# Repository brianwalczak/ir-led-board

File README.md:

# `ir-led-board`
A custom circuit connecting 16 high-current IR LEDs, designed for integration with Raspberry Pi and imaging projects.

Check out my [JOURNAL.md](JOURNAL.md) for updates and progress!

> [!NOTE]  
> All custom footprints in this project, as well as 3D print files, were created by me and are freely available under the MIT license. You are completely welcome to use, modify, and distribute them without any restrictions.

#### PCB Design
A custom-designed printed circuit board, designed in KiCad 9.0, allowing you to control 16 IR LEDs in groups of four. This PCB was designed as an easy way to connect the components and use them via GPIO pins on the Raspberry Pi.

👉 [Read More](KiCad_PCB/README.md)

#### 3D Model (case)
A 3D printable case, designed in Fusion 360, made to securely hold the board and its components, as well as providing protection to prevent damage to the board.

<br>

👉 [Read More](3D_Print/README.md)

#### Bill of Materials (BOM)

| Qty | Part Number                | Total Price |
|-----|------------------------------------------|-------------|
| 5   | JLCPCB: PCB Print               | $5.30      |
| 1   | Raspberry Pi Camera 3 NoIR               | $25.00      |
| 1   | Raspberry Pi 5 Camera Cable              | $1.10       |
| 16  | SFH 4556-AW (850nm IR LEDs)              | $9.47       |
| 16  | CFM12JT43R0 (43 Ohms resistor)           | $0.58       |
| 4   | IRLB8743PBF (MOSFETs)                    | $4.76       |
| 4   | DC0011 (thermal pads)                    | $2.20       |
| 4   | CF14JT100R (100 Ohms resistor)           | $0.24       |
| 4   | CF14JT100K (100K Ohms resistor)          | $0.24       |
| 1   | PPPC061LGBN-RC (90-degree connector)     | $0.57       |
|     | **Total**                                | **$49.46**  |

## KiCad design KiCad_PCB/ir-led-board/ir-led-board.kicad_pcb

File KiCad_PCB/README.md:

# `ir-led-board` - KiCad PCB
> [!NOTE]  
> All custom footprints in this project were created by me and are freely available under the MIT license. You are completely welcome to use, modify, and distribute them without any restrictions.

Welcome! This folder includes a custom-designed printed circuit board for the `ir-led-board`, allowing you to control 16 IR LEDs in groups of four. This PCB was designed as an easy way to connect the components and use them via GPIO pins on the Raspberry Pi.

This PCB was designed in KiCad (you can import it with `File > Open Project` and exported as a ready-to-print Gerber file. This PCB can be printed for about **~$2.00** (quantity of 5) on [JLCPCB](https://jlcpcb.com/) (not sponsored).

**All routing has been automatically done by [Freerouting](https://github.com/freerouting/freerouting): an open-source auto-router for KiCad, built with Java.**

#### Schematic

#### PCB Design

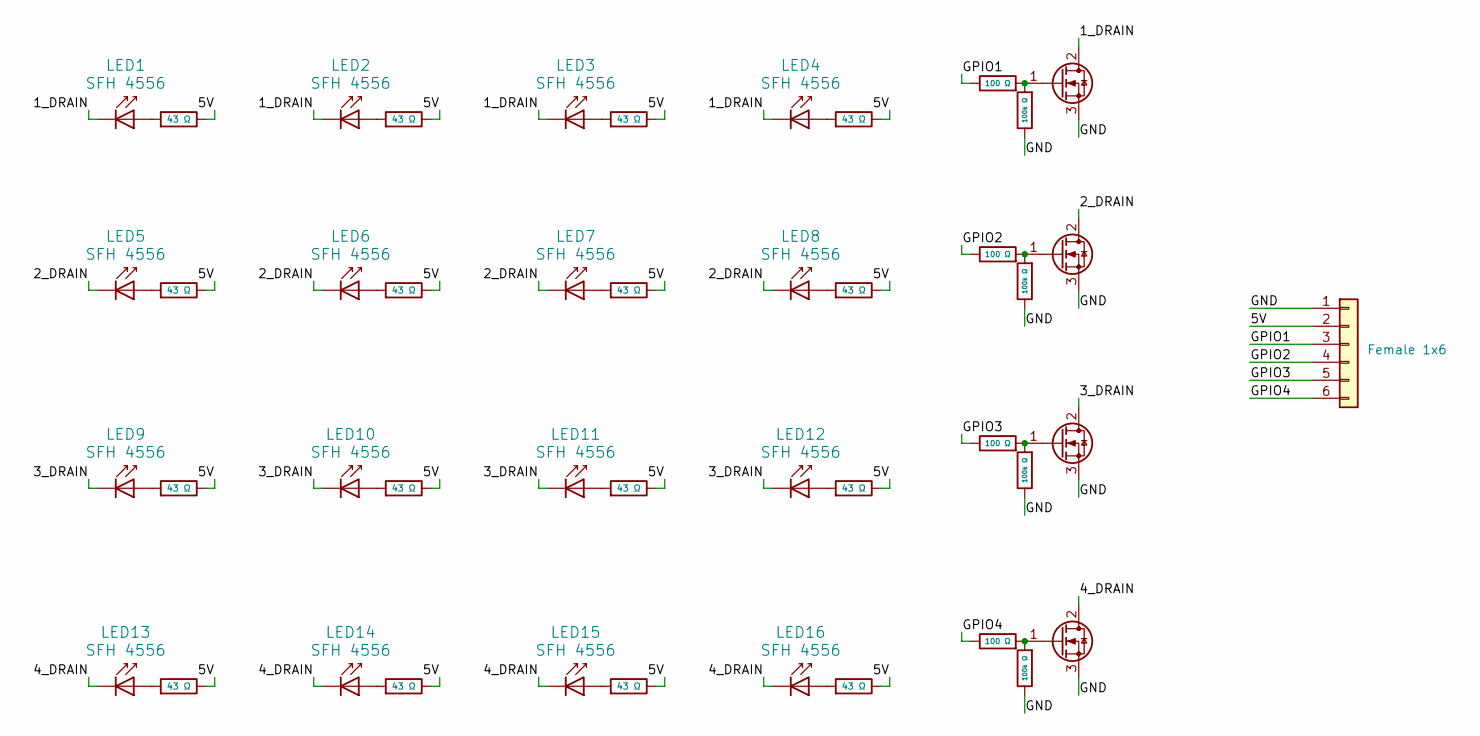
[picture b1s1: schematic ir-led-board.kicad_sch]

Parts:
F1: Female 1x6; PinHeader_1x06_P2.54mm_Horizontal
Group_1, Group_2, Group_3, Group_4: Q_NMOS_GDS; IRLB8743PBF
LED1, LED2, LED3, LED4, LED5, LED6, LED7, LED8, LED9, LED10, LED11, LED12, LED13, LED14, LED15, LED16: SFH 4556; SFH_4556
R1, R2, R3, R4, R5, R6, R7, R8, R9, R10, R11, R12, R13, R14, R15, R16: 43 Ω; CFM12JT43R0
R_100K_1, R_100K_2, R_100K_3, R_100K_4: 100k Ω; CF14JT100K
R_100_1, R_100_2, R_100_3, R_100_4: 100 Ω; CF14JT100R

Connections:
/1_DRAIN: Group_1.2 (D), LED1.1 (K), LED2.1 (K), LED3.1 (K), LED4.1 (K)
/2_DRAIN: Group_2.2 (D), LED5.1 (K), LED6.1 (K), LED7.1 (K), LED8.1 (K)
/3_DRAIN: Group_3.2 (D), LED9.1 (K), LED10.1 (K), LED11.1 (K), LED12.1 (K)
/4_DRAIN: Group_4.2 (D), LED13.1 (K), LED14.1 (K), LED15.1 (K), LED16.1 (K)
/5V: F1.2, R1.1, R2.1, R3.1, R4.1, R5.1, R6.1, R7.1, R8.1, R9.1, R10.1, R11.1, R12.1, R13.1, R14.1, R15.1, R16.1
/GND: F1.1, Group_1.3 (S), Group_2.3 (S), Group_3.3 (S), Group_4.3 (S), R_100K_1.1, R_100K_2.1, R_100K_3.1, R_100K_4.1
/GPIO1: F1.3, R_100_1.1
/GPIO2: F1.4, R_100_2.1
/GPIO3: F1.5, R_100_3.1
/GPIO4: F1.6, R_100_4.1
unnamed: Group_1.1 (G), R_100K_1.2, R_100_1.2
unnamed: Group_2.1 (G), R_100K_2.2, R_100_2.2
unnamed: Group_3.1 (G), R_100K_3.2, R_100_3.2
unnamed: Group_4.1 (G), R_100K_4.2, R_100_4.2
unnamed: LED1.2 (A), R1.2
unnamed: LED2.2 (A), R2.2
unnamed: LED3.2 (A), R3.2
unnamed: LED4.2 (A), R4.2
unnamed: LED5.2 (A), R5.2
unnamed: LED6.2 (A), R6.2
unnamed: LED7.2 (A), R7.2
unnamed: LED8.2 (A), R8.2
unnamed: LED9.2 (A), R9.2
unnamed: LED10.2 (A), R10.2
unnamed: LED11.2 (A), R11.2
unnamed: LED12.2 (A), R12.2
unnamed: LED13.2 (A), R13.2
unnamed: LED14.2 (A), R14.2
unnamed: LED15.2 (A), R15.2
unnamed: LED16.2 (A), R16.2

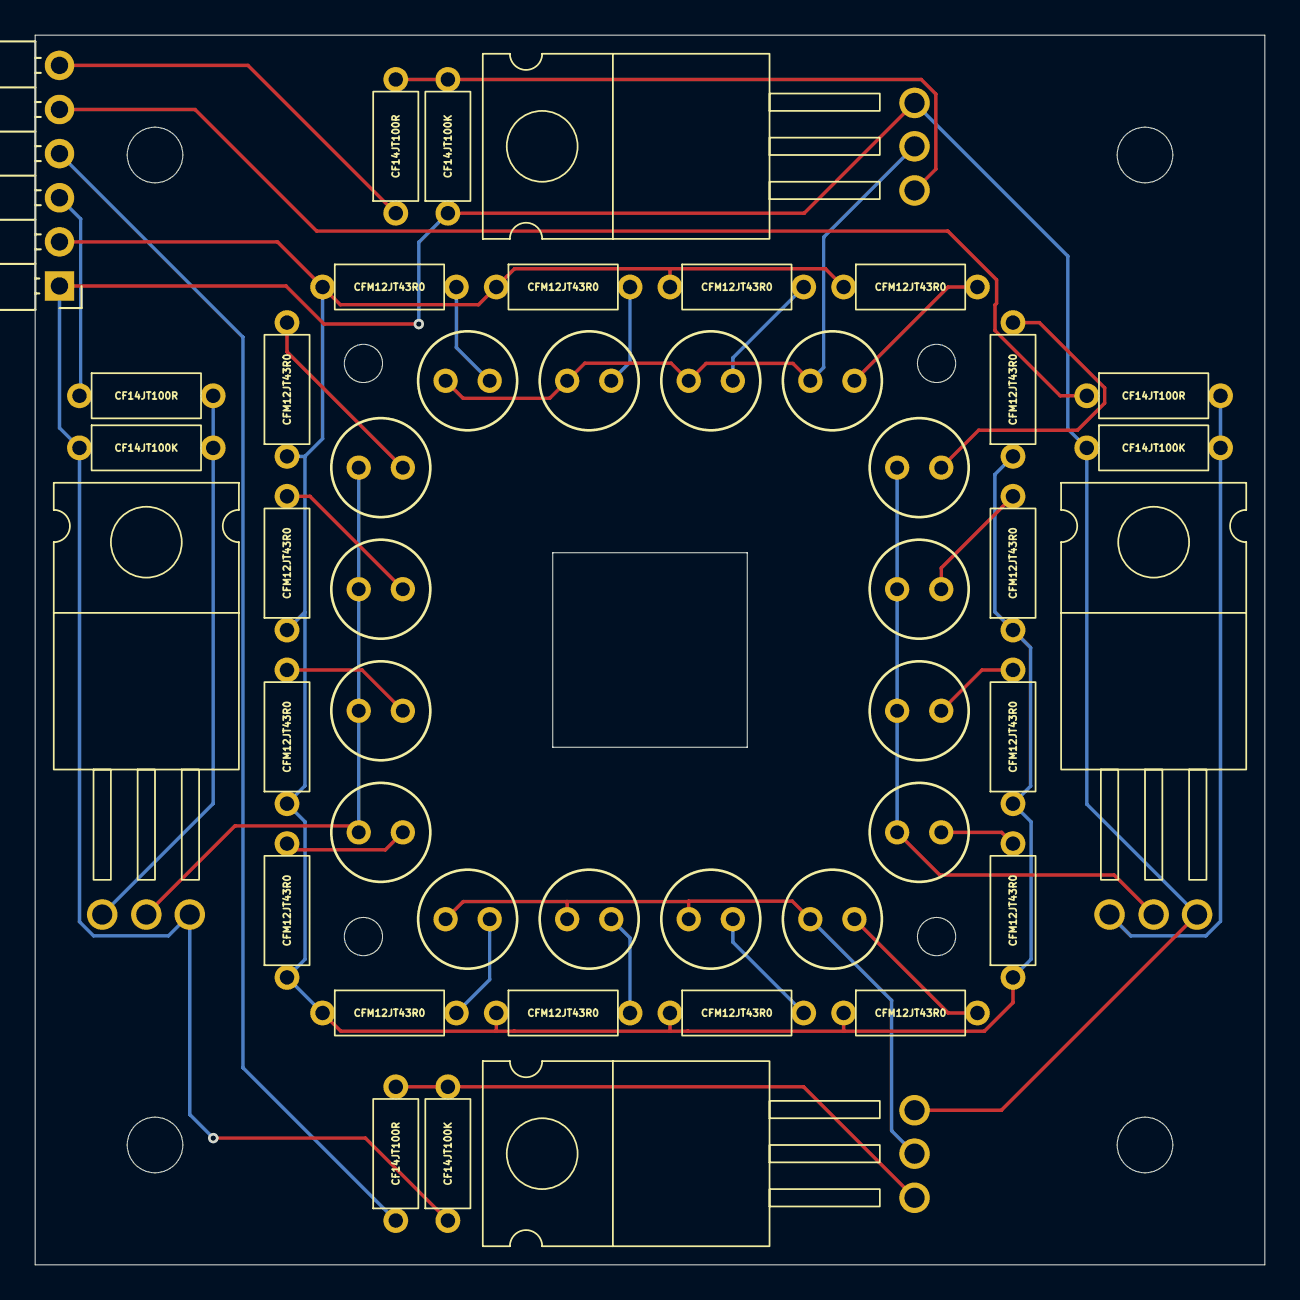
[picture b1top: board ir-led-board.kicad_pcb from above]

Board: 2 copper layers, 70.8 x 70.8 mm, 53 parts (0 on the bottom side), 30 nets.

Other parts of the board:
MOUNT_1, MOUNT_2, MOUNT_3, MOUNT_4: MountingHole_2.2mm_M2
OUTER_MOUNT_1, OUTER_MOUNT_2, OUTER_MOUNT_3, OUTER_MOUNT_4: MountingHole_3.2mm_M3

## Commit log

2025-08-20 Include cart details from DigiKey
2025-08-20 Update images (minor changes)
2025-08-20 Include KiCad files + gerber file
2025-08-21 Add 3D design
2025-08-21 this is what happens when you're tired.. 😴
2025-08-23 Enhance README with PCB and 3D model information
    Added sections for PCB design and 3D model details.
2025-08-24 Add Bill of Materials section to README
    Added a Bill of Materials (BOM) section with details on components and pricing.
2025-08-24 Fix spelling error in README.md
    Corrected the spelling of 'quantity' in the README.
